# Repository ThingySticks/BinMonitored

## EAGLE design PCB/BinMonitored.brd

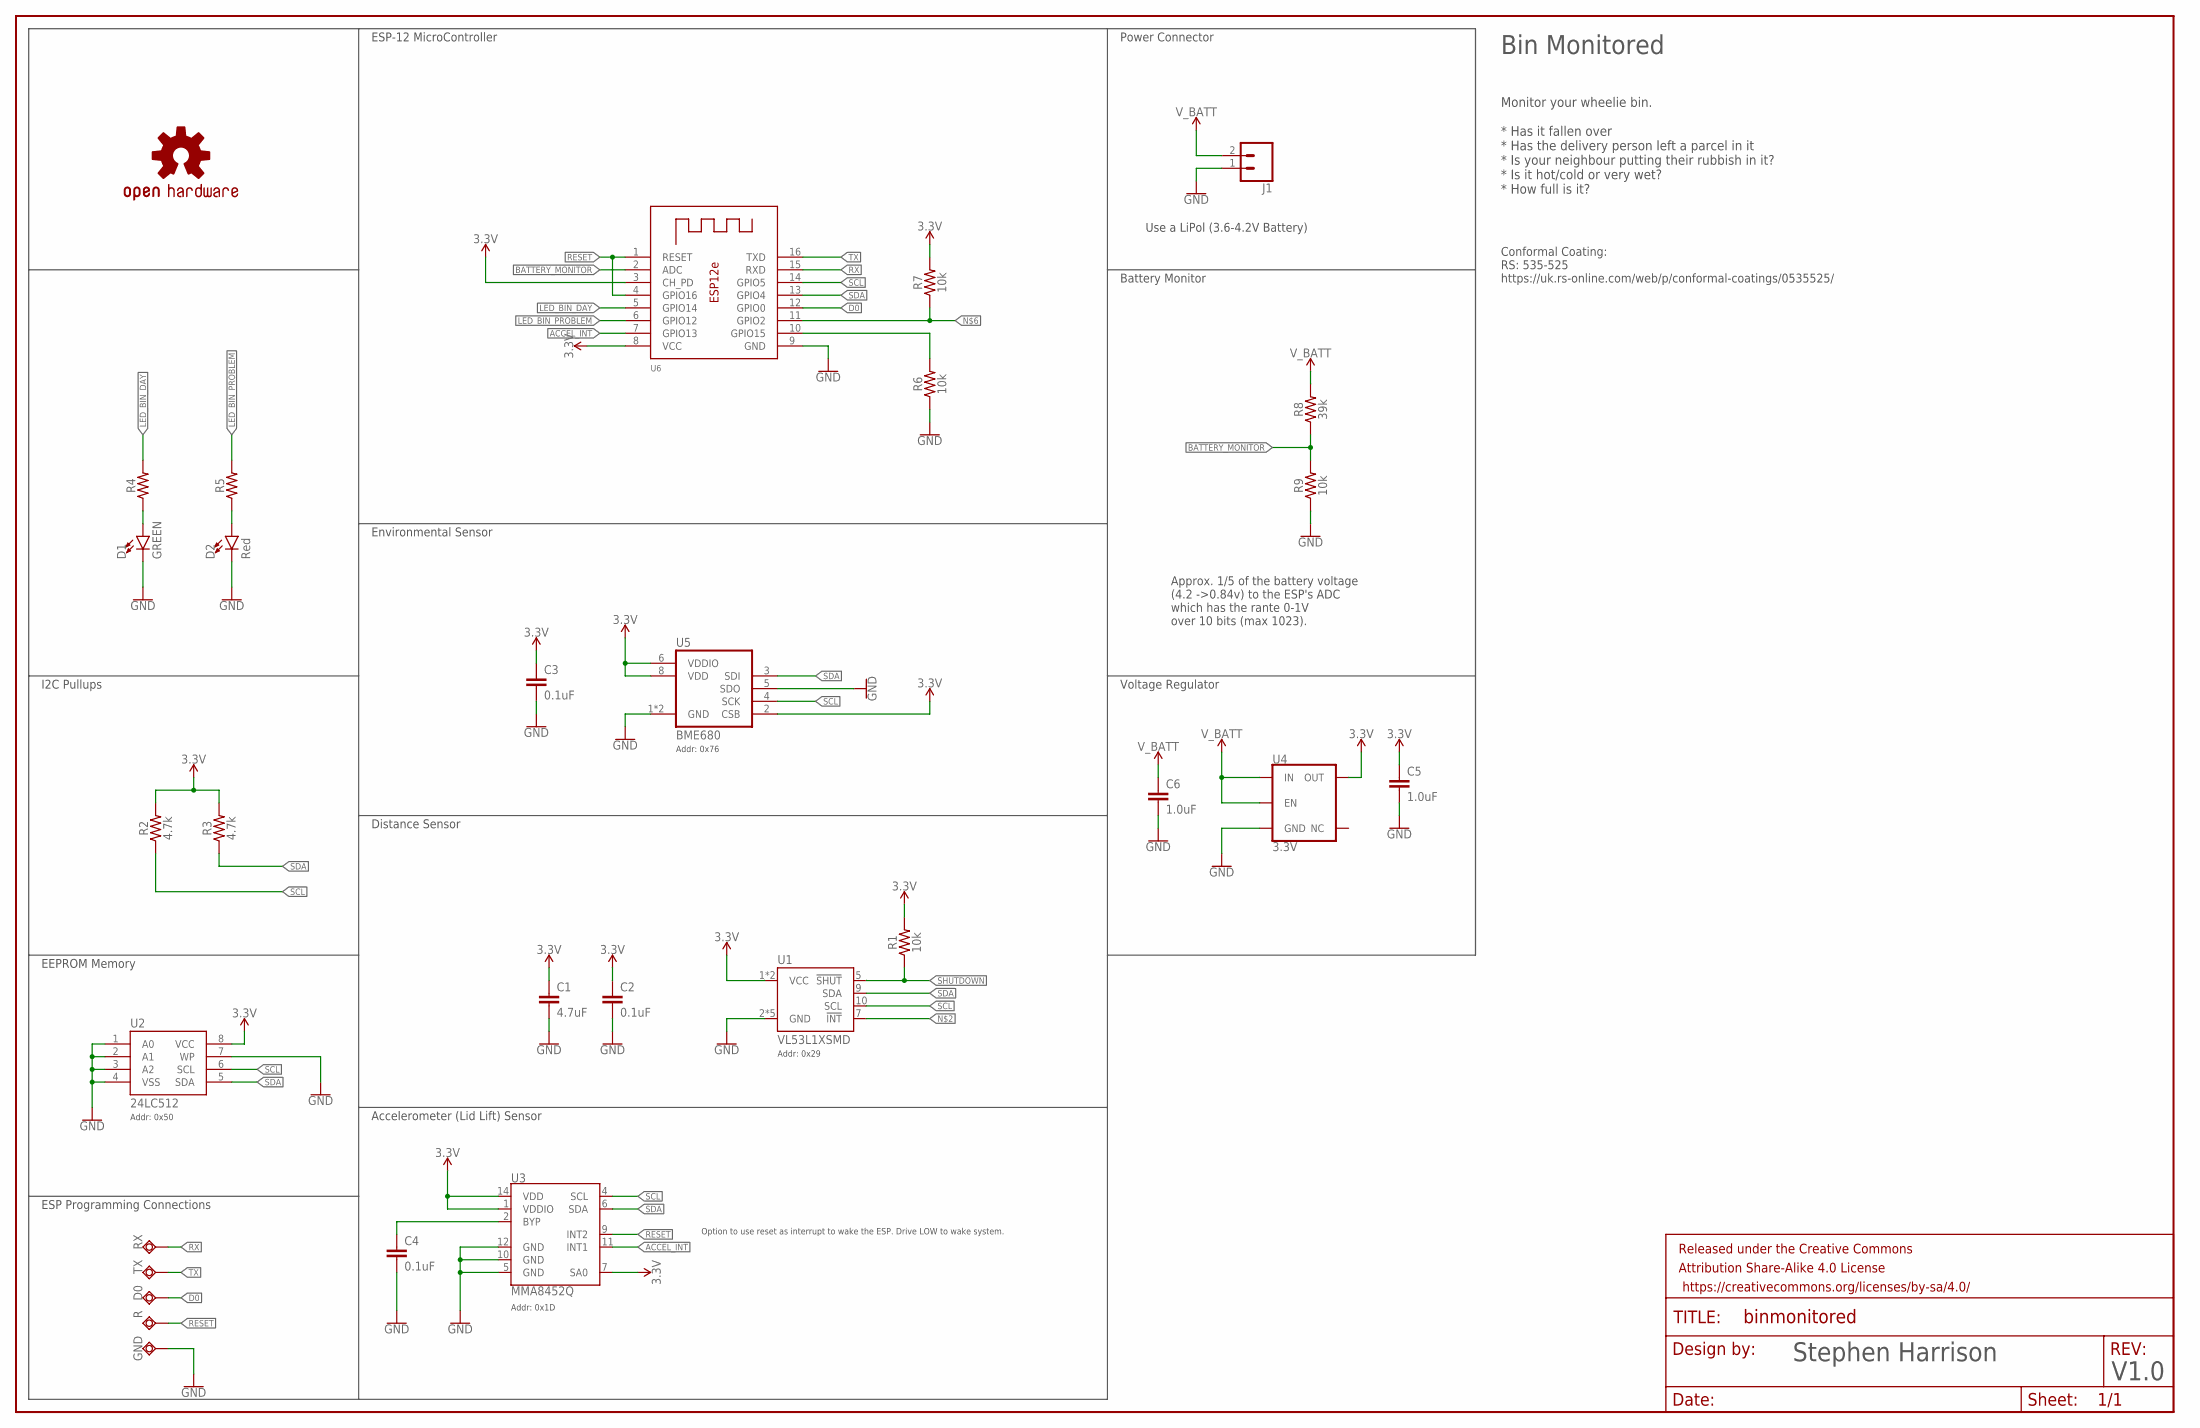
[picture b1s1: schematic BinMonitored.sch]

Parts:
C1: 4.7uF; 0603
C2, C3, C4: 0.1uF; 0603
C5, C6: 1.0uF; 0603
D0: TPSQTP10SQ; TP10SQ
D1: GREEN; LED-1206
D2: Red; LED-1206
FRAME1: FRAME-LEDGER; CREATIVE_COMMONS
GND: TPSQTP10SQ; TP10SQ
J1: CONN_02-JST-2MM-SMT; JST-2-SMD
LOGO1: OSHW-LOGOL; OSHW-LOGO-L
R: TPSQTP10SQ; TP10SQ
R1, R6, R7, R9: 10k; 0603
R2, R3: 4.7k; 0603
R4, R5: 0805
R8: 39k; 0603
RX: TPSQTP10SQ; TP10SQ
TX: TPSQTP10SQ; TP10SQ
U1: VL53L1XSMD; VL53L1X
U2: 24LC512; SO08
U3: MMA8452Q; QFN-16
U4: 3.3V; SOT23-5
U5: BME680
U6: ESP-12E

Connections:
3.3V: C1.1, C2.1, C3.1, C5.1, R1.2, R2.2, R3.2, R7.2, U1.1 (VCC), U1.11 (VCC), U2.8 (VCC), U3.1 (VDDIO), U3.7 (SA0), U3.14 (VDD), U4.5 (OUT), U5.2 (CSB), U5.6 (VDDIO), U5.8 (VDD), U6.3 (CH_PD), U6.8 (VCC)
ACCEL_INT: U3.11 (INT1), U6.7 (GPIO13)
BATTERY_MONITOR: R8.1, R9.2, U6.2 (ADC)
D0: D0.TP, U6.12 (GPIO0)
GND: C1.2, C2.2, C3.2, C4.2, C5.2, C6.2, D1.C, D2.C, GND.TP, J1.1 (2), R6.1, R9.1, U1.2 (GND), U1.3 (GND), U1.4 (GND), U1.6 (GND), U1.12 (GND), U2.1 (A0), U2.2 (A1), U2.3 (A2), U2.4 (VSS), U2.7 (WP), U3.5 (GND), U3.10 (GND), U3.12 (GND), U4.2 (GND), U5.1 (GND), U5.5 (SDO), U5.7 (GND), U6.9 (GND)
GPIO15: R6.2, U6.10 (GPIO15)
LED_BIN_DAY: R4.2, U6.5 (GPIO14)
LED_BIN_PROBLEM: R5.2, U6.6 (GPIO12)
unnamed: R7.1, U6.11 (GPIO2)
unnamed: C4.1, U3.2 (BYP)
unnamed: D1.A, R4.1
unnamed: D2.A, R5.1
RESET: R.TP, U3.9 (INT2), U6.1 (RESET), U6.4 (GPIO16)
RX: RX.TP, U6.15 (RXD)
SCL: R2.1, U1.10 (SCL), U2.6 (SCL), U3.4 (SCL), U5.4 (SCK), U6.14 (GPIO5)
SDA: R3.1, U1.9 (SDA), U2.5 (SDA), U3.6 (SDA), U5.3 (SDI), U6.13 (GPIO4)
SHUTDOWN: R1.1, U1.5 (!SHUT)
TX: TX.TP, U6.16 (TXD)
V_BATT: C6.1, J1.2 (1), R8.2, U4.1 (IN), U4.3 (EN)

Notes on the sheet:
Option to use reset as interrupt to wake the ESP. Drive LOW to wake system.
Addr: 0x29
Addr: 0x76
ESP Programming Connections
EEPROM Memory
I2C Pullups
Power Connector
Use a LiPol (3.6-4.2V Battery)
ESP-12 MicroController
Environmental Sensor
Distance Sensor
Accelerometer (Lid Lift) Sensor
Voltage Regulator
Approx. 1/5 of the battery voltage (4.2 ->0.84v) to the ESP's ADC which has the rante 0-1V over 10 bits (max 1023).
Battery Monitor
Stephen Harrison
V1.0
Bin Monitored
Monitor your wheelie bin. * Has it fallen over * Has the delivery person left a parcel in it * Is your neighbour putting their rubbish in it? * Is it hot/cold or very wet? * How full is it?
Conformal Coating: RS: 535-525 https://uk.rs-online.com/web/p/conformal-coatings/0535525/
Addr: 0x50
Addr: 0x1D

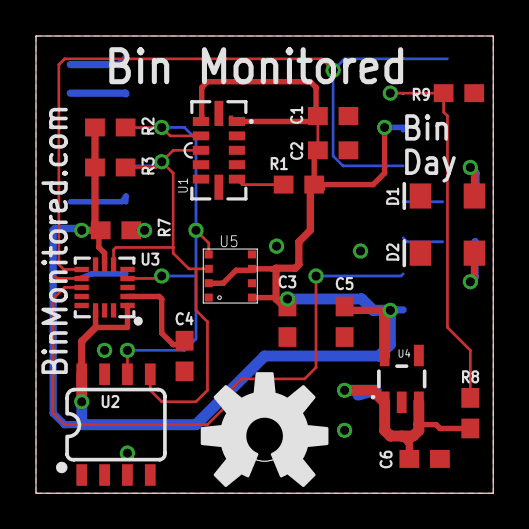
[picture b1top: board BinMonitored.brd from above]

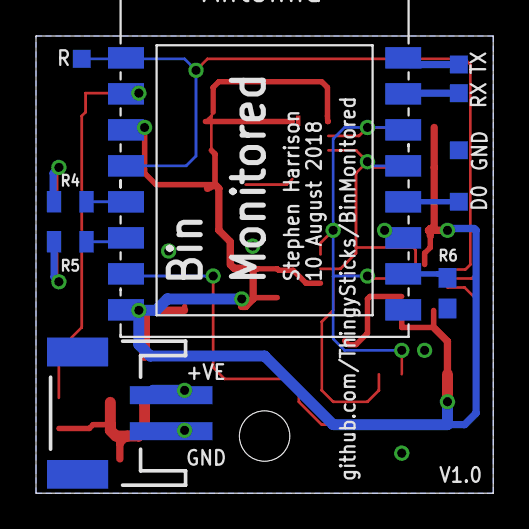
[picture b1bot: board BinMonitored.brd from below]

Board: 2 copper layers, 25.4 x 25.4 mm, 31 parts (10 on the bottom side), 19 nets.

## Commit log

2018-09-13 Initial PCB as sent to OSHPark.
2018-09-13 Added gitignore file.
2018-09-13 Tidied up Schematic and added measurements to the PCB.
2018-09-13 Added images from Eagle export and moved top/bottom image to version subfolder.
2018-09-13 Initial sketch to test out the basics of the sensors and power saving.
2018-09-30 Various improvements for sensor reading, functionality and time.
2018-09-30 Adding helper firmware used for testing the accelerometer.
2018-09-30 Tidyuip for values and text.
2018-09-30 Helper firmware for distance testing.
2018-09-30 Move PCB images.
2018-09-30 Added gerber
2018-09-30 Design files for laser cutting acrylic for the enclosure lid
2018-09-30 Various 3D printable enclosure options and lids.

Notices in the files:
parts and their libraries:
SparkFun-Sensors: Licensing: Creative Commons ShareAlike 4.0 International - https://creativecommons.org/licenses/by-sa/4.0
SparkFun-Aesthetics: Released under the Creative Commons Attribution Share-Alike 4.0 License
SparkFun-Aesthetics: https://creativecommons.org/licenses/by-sa/4.0
